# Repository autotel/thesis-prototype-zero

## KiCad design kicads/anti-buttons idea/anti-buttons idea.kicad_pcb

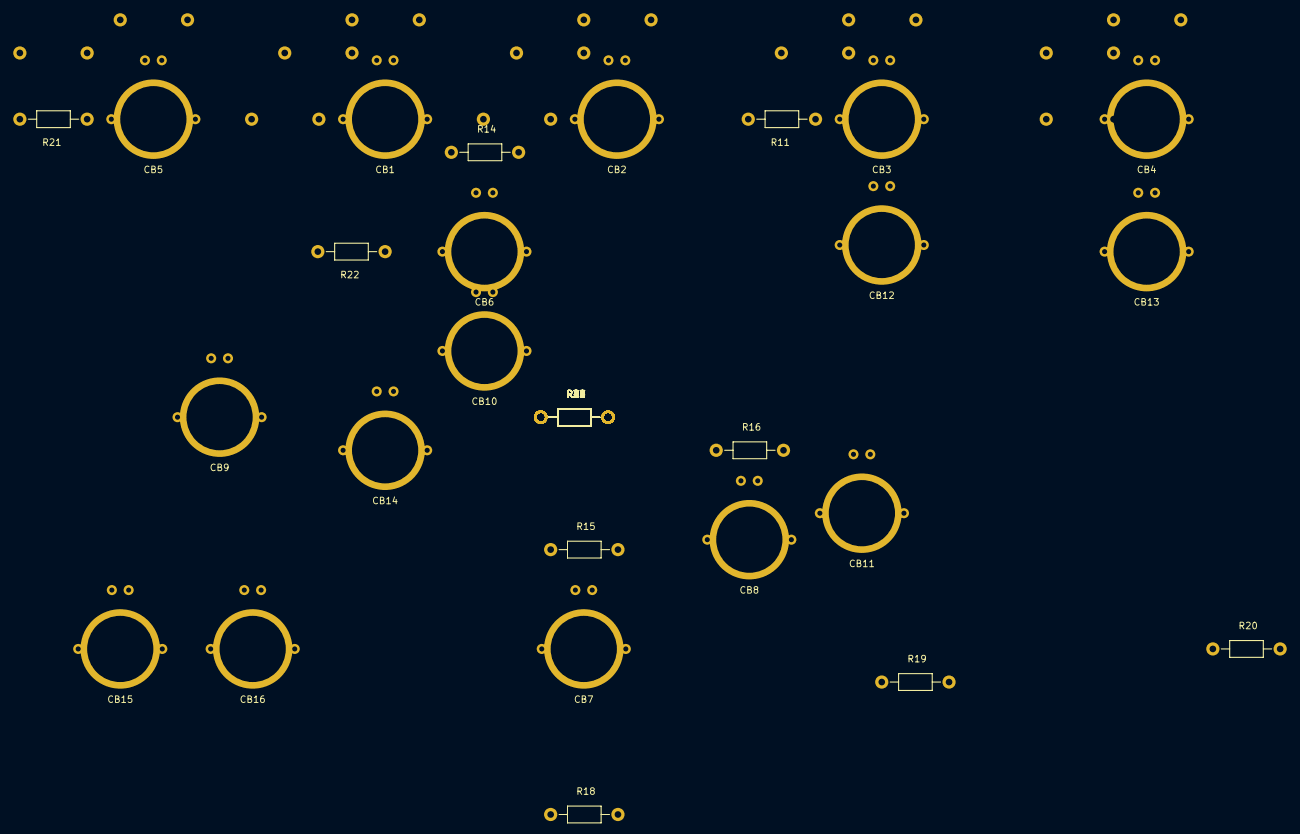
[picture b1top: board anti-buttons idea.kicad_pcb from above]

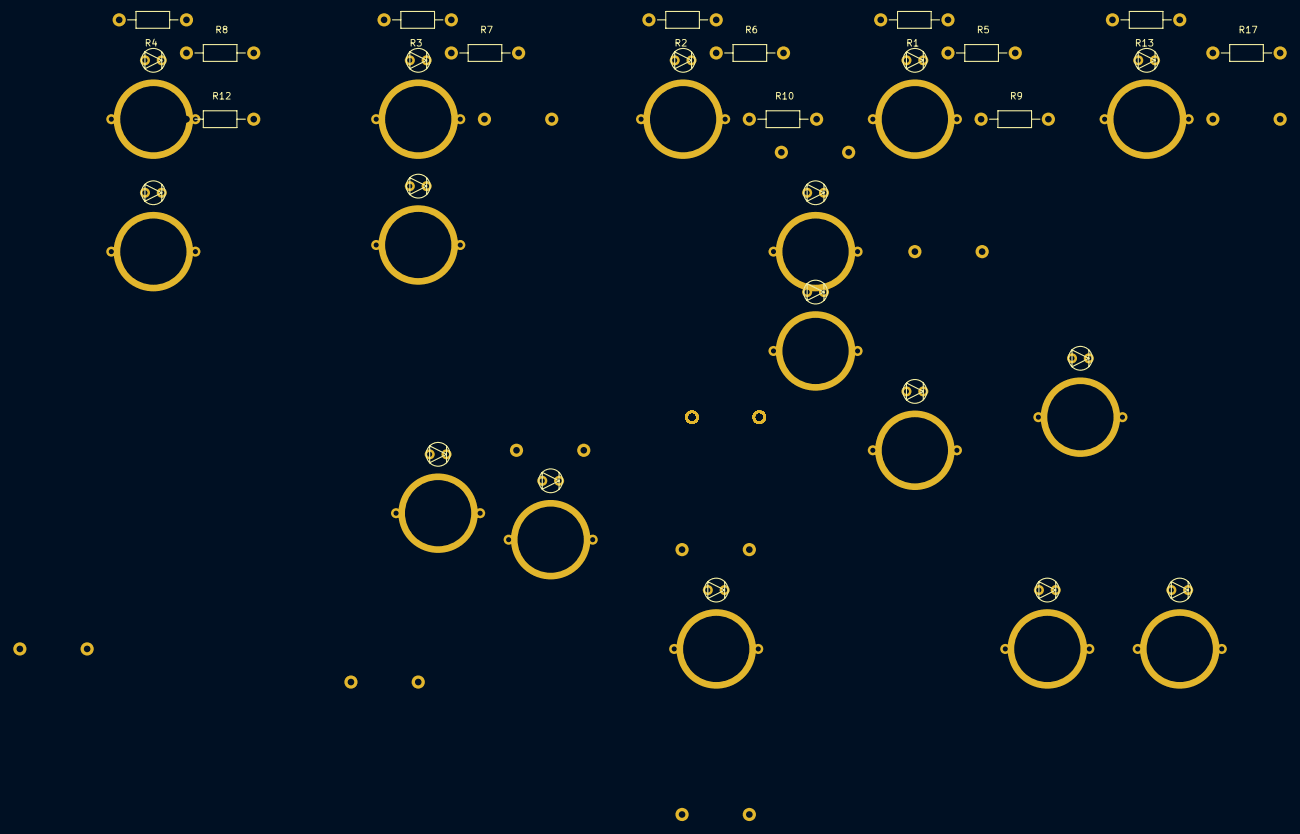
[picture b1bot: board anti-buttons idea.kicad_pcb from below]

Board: 2 copper layers, 64 parts (13 on the bottom side), 48 nets, no tracks yet.

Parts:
CB1, CB2, CB3, CB4, CB5, CB6, CB7, CB8, CB9, CB10, CB11, CB12, CB13, CB14, CB15, CB16: Capacitive-button-01; antiButton-footprint
R1, R2, R3, R4, R13, R14, R15, R16, R25, R26, R27, R28, R37, R38, R39, R40: 1M; Resistor_Horizontal_RM10mm
R5, R6, R7, R8, R17, R18, R19, R20, R29, R30, R31, R32, R41, R42, R43, R44: 150; Resistor_Horizontal_RM10mm
R9, R10, R11, R12, R21, R22, R23, R24, R33, R34, R35, R36, R45, R46, R47, R48: 1K; Resistor_Horizontal_RM10mm

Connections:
unnamed: CB1.2, R1.2
unnamed: CB1.3, R5.1
unnamed: CB1.4, R9.1
unnamed: CB2.2, R2.2
unnamed: CB2.3, R6.1
unnamed: CB2.4, R10.1
unnamed: CB3.2, R3.2
unnamed: CB3.3, R7.1
unnamed: CB3.4, R11.1
unnamed: CB4.2, R4.2
unnamed: CB4.3, R8.1
unnamed: CB4.4, R12.1
unnamed: CB5.2, R13.2
unnamed: CB5.3, R17.1
unnamed: CB5.4, R21.1
unnamed: CB6.2, R14.2
unnamed: CB6.3, R18.1
unnamed: CB6.4, R22.1
unnamed: CB7.2, R15.2
unnamed: CB7.3, R19.1
unnamed: CB7.4, R23.1
unnamed: CB8.2, R16.2
unnamed: CB8.3, R20.1
unnamed: CB8.4, R24.1
unnamed: CB9.2, R25.2
unnamed: CB9.3, R29.1
unnamed: CB9.4, R33.1
unnamed: CB10.2, R26.2
unnamed: CB10.3, R30.1
unnamed: CB10.4, R34.1
unnamed: CB11.2, R27.2
unnamed: CB11.3, R31.1
unnamed: CB11.4, R35.1
unnamed: CB12.2, R28.2
unnamed: CB12.3, R32.1
unnamed: CB12.4, R36.1
unnamed: CB13.2, R37.2
unnamed: CB13.3, R41.1
unnamed: CB13.4, R45.1
unnamed: CB14.2, R38.2
unnamed: CB14.3, R42.1
unnamed: CB14.4, R46.1
unnamed: CB15.2, R39.2
unnamed: CB15.3, R43.1
unnamed: CB15.4, R47.1
unnamed: CB16.2, R40.2
unnamed: CB16.3, R44.1
unnamed: CB16.4, R48.1

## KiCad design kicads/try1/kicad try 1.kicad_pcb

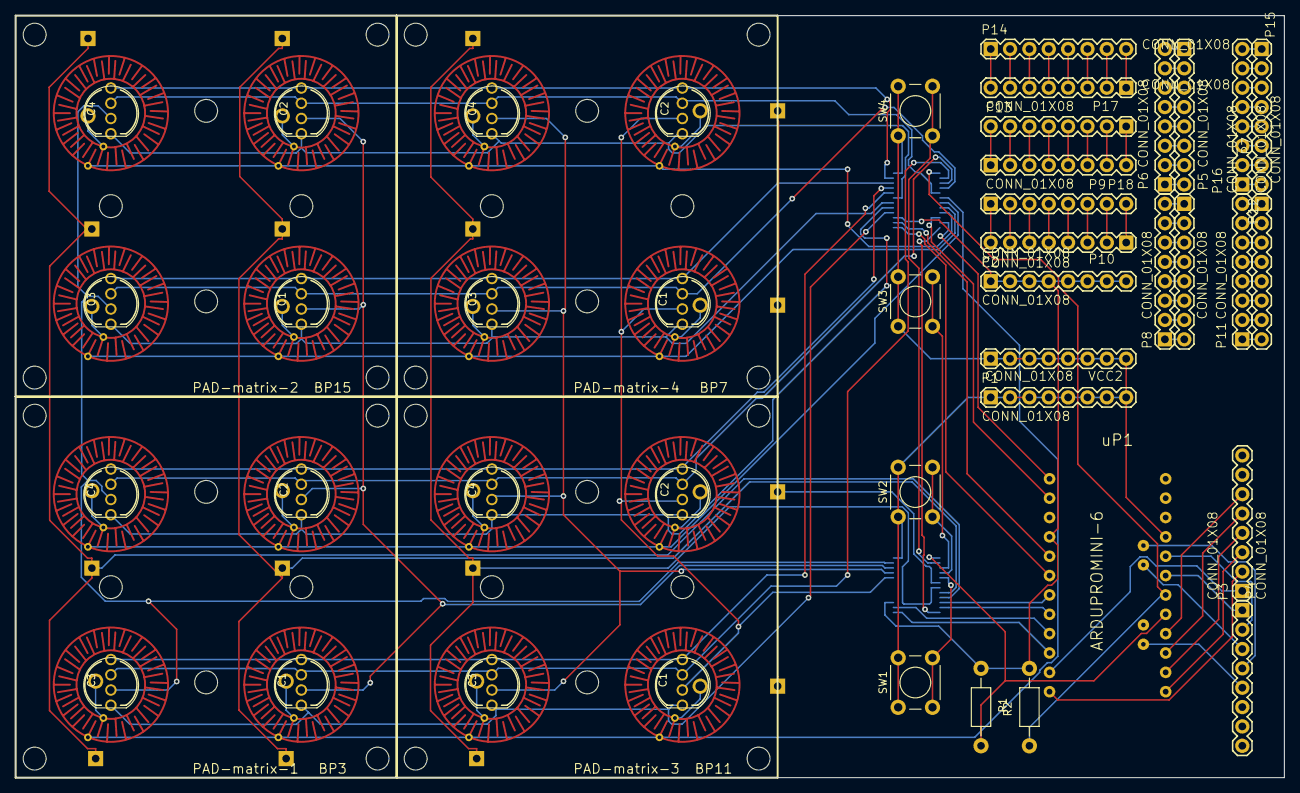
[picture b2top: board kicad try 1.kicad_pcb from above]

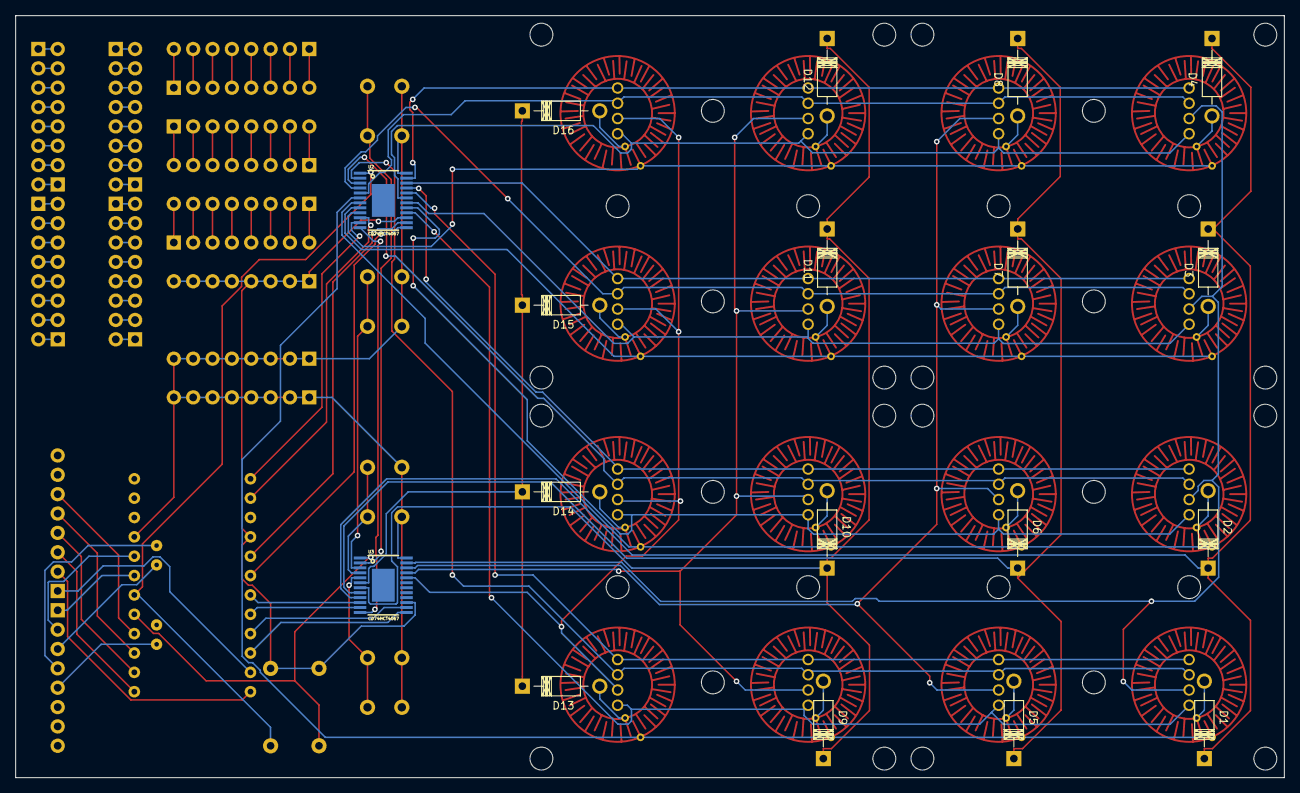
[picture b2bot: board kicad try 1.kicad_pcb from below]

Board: 2 copper layers, 166.5 x 100.0 mm, 48 parts (18 on the bottom side), 124 nets.

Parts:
CONN_01X08: VCC2; 1X08
D1, D2, D3, D4, D5, D6, D7, D8, D9, D10, D11, D12, D13, D14, D15, D16: D; Diode_DO-41_SOD81_Horizontal_RM10
P1, P2, P3, P4, P5, P6, P7, P8, P9, P10, P11, P12, P13, P14, P15, P16, P17, P18: CONN_01X08; 1X08
PAD-matrix-1: BP3; 2x2-buttonpad-sparkfun-autotel
PAD-matrix-2: BP15; 2x2-buttonpad-sparkfun-autotel
PAD-matrix-3: BP11; 2x2-buttonpad-sparkfun-autotel
PAD-matrix-4: BP7; 2x2-buttonpad-sparkfun-autotel
R1, R2: R; Resistor_Horizontal_RM10mm
SW1, SW2, SW3, SW4: SW_PUSH; SW_PUSH_6mm
U2, U3: CD74HCT4067; TSSOP-24
uP1: ARDUPROMINI-6; ArduProMini-6

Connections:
/A0: R2.2, U3.1, uP1.26
/A1: R1.1, U2.1, uP1.25
/A2: P4.1, uP1.24
/A3: P4.2, uP1.23
/A4: P4.3, uP1.32
/A5: P4.4, uP1.31
/A6: P4.5, uP1.35
/MUXAB4: PAD-matrix-2.BLU2, PAD-matrix-2.BLU4, PAD-matrix-4.BLU2, PAD-matrix-4.BLU4, U2.5
/MUXAB5: PAD-matrix-2.BLU1, PAD-matrix-2.BLU3, PAD-matrix-4.BLU1, PAD-matrix-4.BLU3, U2.4
/MUXAB6: PAD-matrix-1.BLU2, PAD-matrix-1.BLU4, PAD-matrix-3.BLU2, PAD-matrix-3.BLU4, U2.3
/MUXAB7: PAD-matrix-1.BLU1, PAD-matrix-1.BLU3, PAD-matrix-3.BLU1, PAD-matrix-3.BLU3, U2.2
/MUXAG8: PAD-matrix-2.GRN2, PAD-matrix-2.GRN4, PAD-matrix-4.GRN2, PAD-matrix-4.GRN4, U2.23
/MUXAG9: PAD-matrix-2.GRN1, PAD-matrix-2.GRN3, PAD-matrix-4.GRN1, PAD-matrix-4.GRN3, U2.22
/MUXAG10: PAD-matrix-1.GRN2, PAD-matrix-1.GRN4, PAD-matrix-3.GRN2, PAD-matrix-3.GRN4, U2.21
/MUXAG11: PAD-matrix-1.GRN1, PAD-matrix-1.GRN3, PAD-matrix-3.GRN1, PAD-matrix-3.GRN3, U2.20
/MUXAR12: PAD-matrix-2.RED2, PAD-matrix-2.RED4, PAD-matrix-4.RED2, PAD-matrix-4.RED4, U2.19
/MUXAR13: PAD-matrix-2.RED1, PAD-matrix-2.RED3, PAD-matrix-4.RED1, PAD-matrix-4.RED3, U2.18
/MUXAR14: PAD-matrix-1.RED2, PAD-matrix-1.RED4, PAD-matrix-3.RED2, PAD-matrix-3.RED4, U2.17
/MUXAR15: PAD-matrix-1.RED1, PAD-matrix-1.RED3, PAD-matrix-3.RED1, PAD-matrix-3.RED3, U2.16
/MUXAS0: PAD-matrix-2.SIG3, PAD-matrix-2.SIG7, PAD-matrix-4.SIG3, PAD-matrix-4.SIG7, U2.9
/MUXAS1: PAD-matrix-2.SIG1, PAD-matrix-2.SIG5, PAD-matrix-4.SIG1, PAD-matrix-4.SIG5, U2.8
/MUXAS2: PAD-matrix-1.SIG3, PAD-matrix-1.SIG7, PAD-matrix-3.SIG3, PAD-matrix-3.SIG7, U2.7
/MUXAS3: PAD-matrix-1.SIG1, PAD-matrix-1.SIG5, PAD-matrix-3.SIG1, PAD-matrix-3.SIG5, U2.6
/MUXBG8: PAD-matrix-1.GND3, PAD-matrix-1.GND4, PAD-matrix-2.GND3, PAD-matrix-2.GND4, U3.23
/MUXBG9: PAD-matrix-1.GND1, PAD-matrix-1.GND2, PAD-matrix-2.GND1, PAD-matrix-2.GND2, U3.22
/MUXBG10: PAD-matrix-3.GND3, PAD-matrix-3.GND4, PAD-matrix-4.GND3, PAD-matrix-4.GND4, U3.21
/MUXBG11: PAD-matrix-3.GND1, PAD-matrix-3.GND2, PAD-matrix-4.GND1, PAD-matrix-4.GND2, U3.20
/MUXBS0: D1.1, D2.1, D3.1, D4.1, U3.9
/MUXBS1: D5.1, D6.1, D7.1, D8.1, U3.8
/MUXBS2: D9.1, D10.1, D11.1, D12.1, U3.7
/MUXBS3: D13.1, D14.1, D15.1, D16.1, U3.6
/MUXBS4: SW1.2, U3.5
/MUXBS5: SW2.2, U3.4
/MUXBS6: SW3.2, U3.3
/MUXBS7: SW4.2, U3.2
/PB0: P3.1, uP1.17
/PB1: P3.2, uP1.18
/PB2: P3.3, uP1.30
/PB3: P3.4, uP1.29
/PB4: P3.5, uP1.28
/PB5: P3.6, uP1.27
/PD0: U2.10, uP1.8
/PD1: U2.11, uP1.7
/PD2: U2.14, uP1.11
/PD3: U2.13, uP1.12
/PD4: U3.10, uP1.13
/PD5: U3.11, uP1.14
/PD6: U3.14, uP1.15
/PD7: U3.13, uP1.16
/VCC: CONN_01X08.1, CONN_01X08.2, CONN_01X08.3, CONN_01X08.4, CONN_01X08.5, CONN_01X08.6, CONN_01X08.7, CONN_01X08.8, P1.1, P1.2, P1.3, P1.4, P1.5, P1.6, P1.7, P1.8, SW1.1, SW2.1, SW3.1, SW4.1, U2.24, U3.24, uP1.22
GND: U2.12, U3.12
GNDREF: P2.1, P2.2, P2.3, P2.4, P2.5, P2.6, P2.7, P2.8, R1.2, R2.1, U2.15, U3.15, uP1.10
unnamed: D1.2, PAD-matrix-1.SIG6
unnamed: D2.2, PAD-matrix-1.SIG8
unnamed: D3.2, PAD-matrix-2.SIG6
unnamed: D4.2, PAD-matrix-2.SIG8
unnamed: D5.2, PAD-matrix-1.SIG2
unnamed: D6.2, PAD-matrix-1.SIG4
unnamed: D7.2, PAD-matrix-2.SIG2
unnamed: D8.2, PAD-matrix-2.SIG4
unnamed: D9.2, PAD-matrix-3.SIG6
unnamed: D10.2, PAD-matrix-3.SIG8
unnamed: D11.2, PAD-matrix-4.SIG6
unnamed: D12.2, PAD-matrix-4.SIG8
unnamed: D13.2, PAD-matrix-3.SIG2
unnamed: D14.2, PAD-matrix-3.SIG4
unnamed: D15.2, PAD-matrix-4.SIG2
unnamed: D16.2, PAD-matrix-4.SIG4
unnamed: P5.1, P6.8
unnamed: P5.2, P6.7
unnamed: P5.3, P6.6
unnamed: P5.4, P6.5
unnamed: P5.5, P6.4
unnamed: P5.6, P6.3
unnamed: P5.7, P6.2
unnamed: P5.8, P6.1
unnamed: P7.1, P8.8
unnamed: P7.2, P8.7
unnamed: P7.3, P8.6
unnamed: P7.4, P8.5
unnamed: P7.5, P8.4
unnamed: P7.6, P8.3
unnamed: P7.7, P8.2
unnamed: P7.8, P8.1
unnamed: P9.8, P10.1
unnamed: P9.7, P10.2
unnamed: P9.6, P10.3
unnamed: P9.5, P10.4
unnamed: P9.4, P10.5
unnamed: P9.3, P10.6
unnamed: P9.2, P10.7
unnamed: P9.1, P10.8
unnamed: P11.1, P12.8
unnamed: P11.2, P12.7
unnamed: P11.3, P12.6
unnamed: P11.4, P12.5
unnamed: P11.5, P12.4
unnamed: P11.6, P12.3
unnamed: P11.7, P12.2
unnamed: P11.8, P12.1
unnamed: P13.1, P14.8
unnamed: P13.2, P14.7
unnamed: P13.3, P14.6
unnamed: P13.4, P14.5
unnamed: P13.5, P14.4
unnamed: P13.6, P14.3
unnamed: P13.7, P14.2
unnamed: P13.8, P14.1
unnamed: P15.1, P16.8
unnamed: P15.2, P16.7
unnamed: P15.3, P16.6
unnamed: P15.4, P16.5
unnamed: P15.5, P16.4
unnamed: P15.6, P16.3
unnamed: P15.7, P16.2
unnamed: P15.8, P16.1
unnamed: P17.1, P18.8
unnamed: P17.2, P18.7
unnamed: P17.3, P18.6
unnamed: P17.4, P18.5
unnamed: P17.5, P18.4
unnamed: P17.6, P18.3
unnamed: P17.7, P18.2
unnamed: P17.8, P18.1

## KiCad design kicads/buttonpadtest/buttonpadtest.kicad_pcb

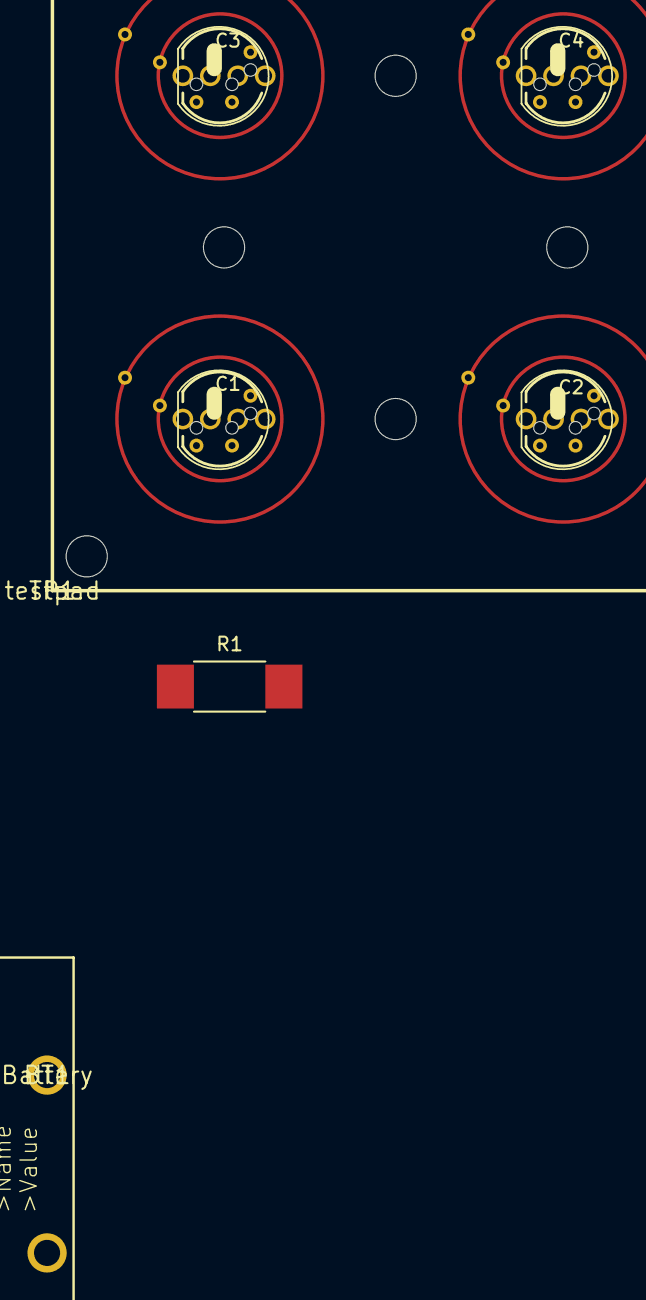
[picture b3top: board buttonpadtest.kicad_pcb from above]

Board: 2 copper layers, 3 parts (0 on the bottom side), 2 nets, no tracks yet.

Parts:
BT1: Battery; BATTCON_9V
R1: R; R_2512_HandSoldering
TP1: testpad; BUTTONPAD-2X2

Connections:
unnamed: R1.1, TP1.BLU6, TP1.GRN6, TP1.RED6, TP1.SIG1
unnamed: R1.2, TP1.GND6, TP1.SIG2

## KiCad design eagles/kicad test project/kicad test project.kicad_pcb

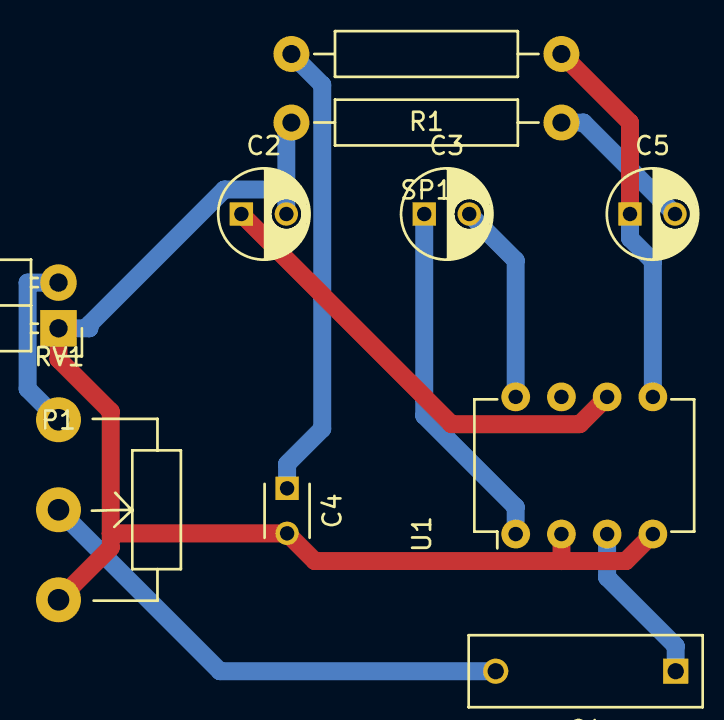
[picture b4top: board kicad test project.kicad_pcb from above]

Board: 2 copper layers, 10 parts (0 on the bottom side), 10 nets.

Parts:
C1: C; C_Rect_L13_W4_P10
C2, C3, C5: CP1; C_Radial_D5_L11_P2.5
C4: C; C_Disc_D3_P2.5
P1: CONN_01X02; Pin_Header_Angled_1x02
R1: R; Resistor_Horizontal_RM15mm
RV1: POT; Potentiometer_WirePads_largePads
SP1: SPEAKER; Resistor_Horizontal_RM15mm
U1: LM386; DIP-8_W7.62mm

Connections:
GNDREF: C2.2, C4.2, P1.1, RV1.3, SP1.2, U1.2, U1.4
unnamed: C1.1, U1.3
unnamed: C1.2, RV1.2
unnamed: C3.1, U1.1
unnamed: C3.2, U1.8
unnamed: C4.1, R1.2
unnamed: C5.1, R1.1, U1.5
unnamed: C5.2, SP1.1
unnamed: P1.2, RV1.1
VCC: C2.1, U1.6

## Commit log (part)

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2016-10-20 lcd working, encoder started
2016-10-26 hello button pads no multiplex (monochrome/row)
2016-10-27 leds now count one by one, completing the matrix program
2016-11-03 change led matrix pins to take them out from audio overlap
2016-11-03 idea for replacing lcd pins
2016-11-08 will not work
2016-11-08 mux is also problematic
2016-11-08 handy notes
2016-11-08 perfect led matrix applied to teensy
2016-11-09 undef var remove
2016-11-10 buttons not yet working but implemented
2016-11-14 buttons and led matrix working
2016-11-15 started pcb design
2016-11-16 first time i think that the schematic is ready
2016-11-16 FIX 16*4 pads error
2016-11-17 forward with the pcb design
2016-11-17 board PCB iteration prior to route
2016-11-17 fix big mistake on schematic
2016-11-17 first successful route
2016-11-18 routing job close
2016-11-18 expose contact terminals in button areas by applying solder mask
2016-11-19 successfully adapted the software for screen+button pad matrix using 16x muxes and arduino
2016-11-19 adapt portb connection to fit an LCD breakout
2016-11-19 routed last schematic change in the dip version
2016-11-22 tried to put ledmatrix libraries inside the libraries but couldn't because problems between static and instance modes that i don't understand
2016-11-28 starting to rollback intent to put all functionality in a library+ addition of barrel jack to pcb
2016-11-28 works, not 'libaried' anymore
2017-01-19 button toggle
2017-01-19 onButtonHeld
2017-01-22 midi style memory and interaction
2017-02-13 screeen slightly better, free up pins for screen
2017-02-13 lcd integrated in hardware
2017-02-14 more comments, activated intervace tact switches and duplicated to make a version with ui
2017-02-14 selector buttons now have onpress and onrelease funcs modeselector base
2017-02-14 modeselector is a modifier and not a mode
2017-02-14 cmplete ability to select channels, notes and playing modes using different user interaction schemes
2017-02-14 -split in multiple files - created the interaction for the scale design mode
2017-02-14 prototypes of cc modulation along with notes
2017-02-15 encoder activated notes for improvement of the PCB board
2017-02-16 body for the v2 prorotype started additional notes on the pcb design
2017-02-17 started creating the way for the sequencer, including changes in the ui and memory optimization fixed errors in the enclosure. There are still some to fix
2017-02-18 reduced use of dynamic memory by storing strings in PROGMEM
2017-02-18 basic and buggy implementation of sequencer mode with less memory usage
2017-02-28 checking different screen algorhythms to correct the problems
2017-02-28 changed some hardcoded vars with preprocessor vars
2017-03-02 fixed all known trouble with note matching in sequencer
2017-03-02 -fixed binding between matrix seleectors and the selected item (example: when selecting channel, buttons display last pressed button instead of actually selected channel, now they would represent the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
2017-03-02 - fix channel can't be selected scrolling, and modularized modes and POVS to avoid array index out of bounds when selecting higher ¨POV or MODE than available - put order in selector modes. there is 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
2017-03-03 many minor fixes
2017-03-03 started creating the function to find events in the perspective of ynamic modulus
2017-03-03 -rename pm_current with pov_current -more intuitive quantization when recording performance follows neares beat instead of currently running beat
2017-03-03 finished implementing the modulus based composition, but it takes a huge stake on processor time
2017-04-19 double microcontroller
2017-04-19 eliminate memory functions from display arduino
2017-05-09 testing using serial with node. the linbrary sucks bad
2017-05-10 figured out two way communication via serial (raspberry) and Fixed screen flickering!!
2017-05-10 stress testing the serial based physical interface showing good results
2017-05-11 can output midi using an usb midi interface
2017-05-11 files tidy up
2017-05-11 the firmware and the javascript script share the same constants
2017-05-11 trying to send strings didn't work
2017-05-12 set communicatiin trhough usb due to hardware problems, started testing interaction modes that are handled by the interface
2017-05-12 use arduino as screen for the raspberry maning that all data is handled in raspberry, and only grpahics data is sent to the arduino
2017-05-12 segregated interaction modes javascript node brain
2017-05-12 index on virtual-modular-uno-is-screen: 5c9fb7c hardware manager is part of environment so mode handlers can draw
2017-05-12 nice reduction of stuff in arduino, but still can't figure out why it doesnt work
2017-05-12 could write to the led matrix from the main index js but now the communication back is corrupted
2017-05-12 kind of working
2017-05-17 free the serial pins replacing them with two analog pins. generated problem with refresh rate
2017-05-17 fixed problem with refresh rate was due to making a softwareserial using the hardware serial pins, probably using inverted RX TX pin roles
2017-05-17 move the screen a bit up so it fits with the actual pcb
2017-05-17 same mapping for void readMuxB
2017-05-17 fix couple of errors in last commit
2017-05-17 prototype for reception of typed arrays of different lengths
2017-05-17 typed message with many lengths implemented using real constants
2017-05-17 node cuts and receives messages properly according to constants lengths
2017-05-17 fixed some issues with communication. still problems with transmision of pixels
2017-05-18 found solution to commmunication problem. it was because message didn't arrive complete yet when it was already out of the receiving loop. the message slicing should be done in the reception loop, an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
2017-05-18 implemented the same algorythm in the arduino side than in the node side, eliminating the requirement to delay() to receive the whole message. works like a charm
2017-05-18 mode engagement, and handling of metronome steps in modes there was a confilct where a mode that is not engaged will override the screen display of other modes if it had a listener that required scre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
2017-05-18 implemented a n-length data serial transmission
2017-05-19 sequencer dimension selector submode
2017-05-19 basic code cleaning in the firmware
2017-05-19 a bit healthier message sending, using a global array instead of local
2017-05-19 designing how the note is input in the sequencer
2017-05-19 implementing midi notes and interaction with scale setter
2017-05-22 implementing better filters will need to reestructure destinations
2017-05-22 many sequencers, finished implementing better filters and changing the interaction for layering
2017-05-22 fixed many severe errors that were curiously not causing problems. perhaps these were the origin of serial noise
2017-05-22 program encoder press detection which is not working anyways
2017-05-22 half way doing the preset kit creator
2017-05-23 a bit better interaction with system mode
2017-05-24 truncate screen messages to space available
2017-05-24 loop length and displace selector
2017-05-26 finished adding sequencer event filtering, started implementing note lengths
2017-05-26 implemented note lengths in sequencer, with some bugs
2017-05-26 loop look can be turned off
2017-05-26 created pat length folding, but still implementing the events duplicator
2017-05-28 less console logs, don't propagate null messages to event handler
2017-05-28 I apparently fixed the communication problem with the harware that was haunting.
2017-05-28 fixed that event emission from kit went off when I chaged dimension selector remove some console.logs
2017-06-01 change start command bacause with sound was too slow
2017-06-01 copy base of server taken from node-patternplatform; not integrated yet
2017-06-01 rename 'destinations' as 'modules' gives clearer idea of function behind
2017-06-01 reestructure server as optional subsidiary of environment changed how patcher modules are created in order to create event handlers more easily
2017-06-01 more general structure of the server
2017-06-02 framework that allows one server side module to be represented by several force directed nodes
2017-06-02 rename modes into modulex16 interfaces, will suggest how to add different hardware support in the future and is easier to understand
2017-06-02 reestructuration continues created an add module interaction mode, renamed some variables and files modules are singletons that can create instances dynamic elements naming changed more structures
2017-06-02 make singleton-instanced structures of the interaction modes similar to the one of the modules. rename interaction modes by type
2017-06-03 finally closed the loop of dynamically adding a module with it's interface
2017-06-03 further with the modular reestructuring
2017-06-03 loading default config from json didnt allow for more than one copy of each type of module. now it allows
2017-06-04 started to separate the sequencer between interface and function
2017-06-04 segregation of the sequencer: it runs, but not finsihed yet
2017-06-04 clear console.logs
2017-06-05 links data binding
2017-06-06 emission of eventMessages to clientside
2017-06-06 clocks were not emitting sub there was an error evaluating wether message had sub, because 0 evaluates false
2017-06-06 kit controller was not multi instanceable sequencer was not eventing the subs well
2017-06-06 preset kit was not propagating received messages,
2017-06-06 change forces a bit
2017-06-07 anti drifting 1
2017-06-07 loop folding would remove all the pattern if it was being shrunk rename controlledDestination into controlledModule in many modulecontrollers to give a clearer idea of the var
2017-06-07 sequencer loop displace
2017-06-07 fixed a bug where step events created by the folder were wrong
2017-06-07 loop folding was not propagaing to loop length actually
2017-06-08 muting presets presetkit
2017-06-08 better quantization for recorded sequencer events fixed yet another error in the muting of the presetkit
2017-06-08 note lengths were not being recorded
2017-06-08 sequencers have clock input by default, if there is a bus named "deft. clock bus" to make it easier
2017-06-09 sequencer that received a new recorded pat will switch to the destination that will show the new events
2017-06-09 add a special mark if the same module is chosen as output
2017-06-09 fixed mistake in previus commit
2017-06-09 the clock is now apparently perfect
2017-06-10 fixed modules muting and make noteoff on param change in presetkit
2017-06-10 fix mistake
2017-07-07 fixed problem of double triggering while recording, that was due to wrong event quantization
2017-07-07 make grade just work
2017-07-14 create chordkit interaction
2017-07-20 added raspberry anchoring holes and ventilation
2017-07-20 todos for 31st presentation
2017-07-20 half way implementing performance and recording in chordkit
2017-07-21 chordkit is working recording broke for some reason
2017-07-25 add "transparent" events, solve some errors in chordKit, eventMessage super and underimpose
2017-07-25 precarious implementation of basenote in the chordkit
2017-07-26 fix many errors with the chordkit
2017-07-27 after many tries, I resolved to implement a recording that chooses wether to record modules ui input or module's output, potentially allowing two features that were wanted
2017-07-27 two-folded recording from chordkit aswell
2017-07-27 display lengths of notes, also when creating a new note in a sequencer
2017-07-27 muting a sequencer would most likely generate hanging notes because the noteoff tracker was muted aswell
2017-07-27 show current selected preset presetkit
2017-09-29 cleanup of kicad folder
2017-09-29 cleanup kicad
2017-09-29 redesign of specs after experimenting and thinking
2017-09-29 improvement of last commit
2017-09-29 restart sequencer with a selector button combination+matrix button
